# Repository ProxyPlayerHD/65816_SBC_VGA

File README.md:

# 65816 VGA Card
This is a simple VGA Expansion card designed for my 65816 SBC<br>
It uses an `ATF1508AS` CPLD for all the Logic, and 4x `IDT7005S` or `IDT7006S` Dual Port SRAM ICs for a total of either 32kB or 64kB of VRAM. (or something inbetween)

the Logic uploaded here is for 32kB of VRAM, 640x400 Monochrome (1 bit per pixel or "bpp") with an Interrupt every time a frame finished drawing.<br>
Though once i get my hands on some 16kB Chips i'll likely do a few more versions of the Logic and also upload them here.

# Folders
* "Downloaded Libs" contains the symbols and footprints for the KiCad Project
* "Logic" contains the... well Logic for the entire thing. i've included the original .dig file (requires [Digital](https://github.com/hneemann/Digital) to open), and already generated .v (Verilog) and .pof/.jed (program files in case you want to skip setting up Quartus to generate them yourself)
* "Gerbers" contains all required Gerbers to order yourself the PCB

# Misc

regards to the Logic:
the `CA13` line (CPU Address bit 13) is only required when dealing with 8kB DP-SRAM Chips,<br>
and the `VA13` (Video Address bit 13) line is only required when dealing with 16kB DP-SRAM Chips.<br>
also right now the decoding logic puts the VRAM on the CPU side at address `$FF8000`

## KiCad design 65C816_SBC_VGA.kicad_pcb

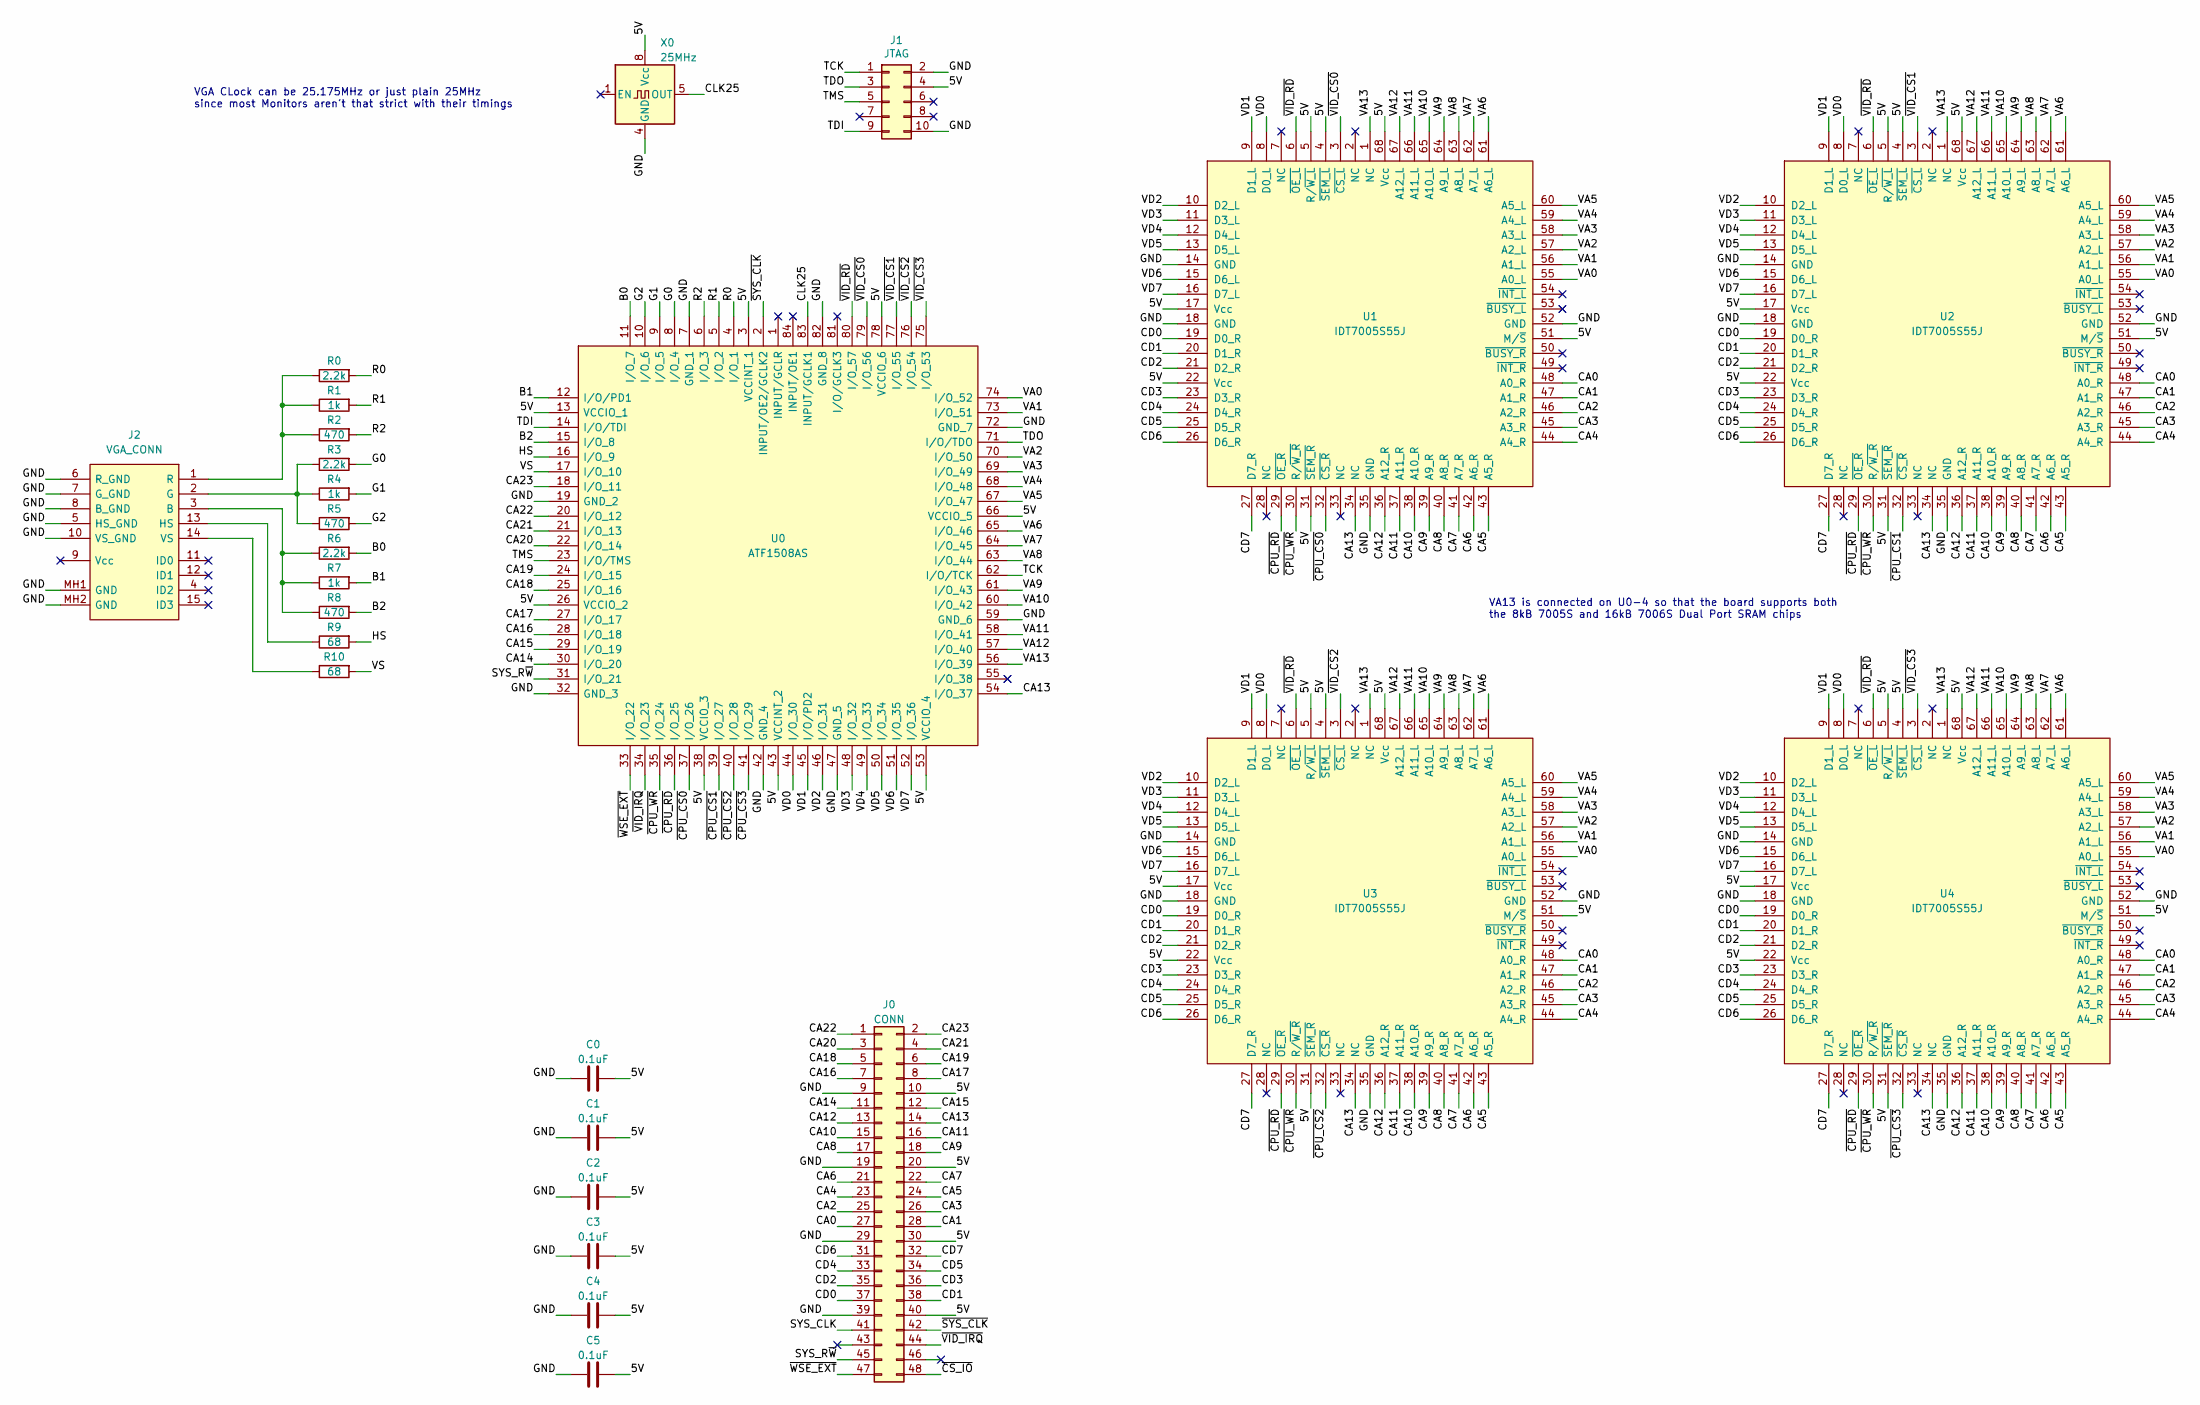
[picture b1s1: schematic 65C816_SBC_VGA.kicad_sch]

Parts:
C0, C1, C2, C3, C4, C5: 0.1uF; C_Disc_D4.3mm_W1.9mm_P5.00mm
J0: CONN; CARD_EDGE
J1: JTAG; PinHeader_2x05_P2.54mm_Vertical
J2: VGA_CONN; Mouser Part Number 156-3315-E
R0, R3, R6: 2.2k; R_Axial_DIN0207_L6.3mm_D2.5mm_P2.54mm_Vertical
R1, R4, R7: 1k; R_Axial_DIN0207_L6.3mm_D2.5mm_P2.54mm_Vertical
R2, R5, R8: 470; R_Axial_DIN0207_L6.3mm_D2.5mm_P2.54mm_Vertical
R9, R10: 68; R_Axial_DIN0207_L6.3mm_D2.5mm_P2.54mm_Vertical
U0: ATF1508AS; PLCC-84_THT-Socket
U1, U2, U3, U4: IDT7005S55J; PLCC-68_THT-Socket
X0: 25MHz; Oscillator_DIP-8

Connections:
/5V: C0.2, C1.2, C2.2, C3.2, C4.2, C5.2, J0.10, J0.20, J0.30, J0.40, J1.4, U0.3 (VCCINT_1), U0.13 (VCCIO_1), U0.26 (VCCIO_2), U0.38 (VCCIO_3), U0.43 (VCCINT_2), U0.53 (VCCIO_4), U0.66 (VCCIO_5), U0.78 (VCCIO_6), U1.4 (~SEM_L), U1.5 (R/~W_L), U1.17 (Vcc), U1.22 (Vcc), U1.31 (~SEM_R), U1.51 (M/~S), U1.68 (Vcc), U2.4 (~SEM_L), U2.5 (R/~W_L), U2.17 (Vcc), U2.22 (Vcc), U2.31 (~SEM_R), U2.51 (M/~S), U2.68 (Vcc), U3.4 (~SEM_L), U3.5 (R/~W_L), U3.17 (Vcc), U3.22 (Vcc), U3.31 (~SEM_R), U3.51 (M/~S), U3.68 (Vcc), U4.4 (~SEM_L), U4.5 (R/~W_L), U4.17 (Vcc), U4.22 (Vcc), U4.31 (~SEM_R), U4.51 (M/~S), U4.68 (Vcc), X0.8 (Vcc)
/B0: R6.2, U0.11 (I/O_7)
/B1: R7.2, U0.12 (I/O/PD1)
/B2: R8.2, U0.15 (I/O_8)
/CA0: J0.27, U1.48 (A0_R), U2.48 (A0_R), U3.48 (A0_R), U4.48 (A0_R)
/CA1: J0.28, U1.47 (A1_R), U2.47 (A1_R), U3.47 (A1_R), U4.47 (A1_R)
/CA2: J0.25, U1.46 (A2_R), U2.46 (A2_R), U3.46 (A2_R), U4.46 (A2_R)
/CA3: J0.26, U1.45 (A3_R), U2.45 (A3_R), U3.45 (A3_R), U4.45 (A3_R)
/CA4: J0.23, U1.44 (A4_R), U2.44 (A4_R), U3.44 (A4_R), U4.44 (A4_R)
/CA5: J0.24, U1.43 (A5_R), U2.43 (A5_R), U3.43 (A5_R), U4.43 (A5_R)
/CA6: J0.21, U1.42 (A6_R), U2.42 (A6_R), U3.42 (A6_R), U4.42 (A6_R)
/CA7: J0.22, U1.41 (A7_R), U2.41 (A7_R), U3.41 (A7_R), U4.41 (A7_R)
/CA8: J0.17, U1.40 (A8_R), U2.40 (A8_R), U3.40 (A8_R), U4.40 (A8_R)
/CA9: J0.18, U1.39 (A9_R), U2.39 (A9_R), U3.39 (A9_R), U4.39 (A9_R)
/CA10: J0.15, U1.38 (A10_R), U2.38 (A10_R), U3.38 (A10_R), U4.38 (A10_R)
/CA11: J0.16, U1.37 (A11_R), U2.37 (A11_R), U3.37 (A11_R), U4.37 (A11_R)
/CA12: J0.13, U1.36 (A12_R), U2.36 (A12_R), U3.36 (A12_R), U4.36 (A12_R)
/CA13: J0.14, U0.54 (I/O_37), U1.34 (NC), U2.34 (NC), U3.34 (NC), U4.34 (NC)
/CA14: J0.11, U0.30 (I/O_20)
/CA15: J0.12, U0.29 (I/O_19)
/CA16: J0.7, U0.28 (I/O_18)
/CA17: J0.8, U0.27 (I/O_17)
/CA18: J0.5, U0.25 (I/O_16)
/CA19: J0.6, U0.24 (I/O_15)
/CA20: J0.3, U0.22 (I/O_14)
/CA21: J0.4, U0.21 (I/O_13)
/CA22: J0.1, U0.20 (I/O_12)
/CA23: J0.2, U0.18 (I/O_11)
/CD0: J0.37, U1.19 (D0_R), U2.19 (D0_R), U3.19 (D0_R), U4.19 (D0_R)
/CD1: J0.38, U1.20 (D1_R), U2.20 (D1_R), U3.20 (D1_R), U4.20 (D1_R)
/CD2: J0.35, U1.21 (D2_R), U2.21 (D2_R), U3.21 (D2_R), U4.21 (D2_R)
/CD3: J0.36, U1.23 (D3_R), U2.23 (D3_R), U3.23 (D3_R), U4.23 (D3_R)
/CD4: J0.33, U1.24 (D4_R), U2.24 (D4_R), U3.24 (D4_R), U4.24 (D4_R)
/CD5: J0.34, U1.25 (D5_R), U2.25 (D5_R), U3.25 (D5_R), U4.25 (D5_R)
/CD6: J0.31, U1.26 (D6_R), U2.26 (D6_R), U3.26 (D6_R), U4.26 (D6_R)
/CD7: J0.32, U1.27 (D7_R), U2.27 (D7_R), U3.27 (D7_R), U4.27 (D7_R)
/CLK25: U0.83 (INPUT/GCLK1), X0.5 (OUT)
/G0: R3.2, U0.8 (I/O_4)
/G1: R4.2, U0.9 (I/O_5)
/G2: R5.2, U0.10 (I/O_6)
/GND: C0.1, C1.1, C2.1, C3.1, C4.1, C5.1, J0.9, J0.19, J0.29, J0.39, J1.2, J1.10, J2.5 (HS_GND), J2.6 (R_GND), J2.7 (G_GND), J2.8 (B_GND), J2.10 (VS_GND), J2.MH1 (GND), J2.MH2 (GND), U0.7 (GND_1), U0.19 (GND_2), U0.32 (GND_3), U0.42 (GND_4), U0.47 (GND_5), U0.59 (GND_6), U0.72 (GND_7), U0.82 (GND_8), U1.14 (GND), U1.18 (GND), U1.35 (GND), U1.52 (GND), U2.14 (GND), U2.18 (GND), U2.35 (GND), U2.52 (GND), U3.14 (GND), U3.18 (GND), U3.35 (GND), U3.52 (GND), U4.14 (GND), U4.18 (GND), U4.35 (GND), U4.52 (GND), X0.4 (GND)
/HS: R9.2, U0.16 (I/O_9)
/R0: R0.2, U0.4 (I/O_1)
/R1: R1.2, U0.5 (I/O_2)
/R2: R2.2, U0.6 (I/O_3)
/SYS_CLK: J0.41
/SYS_R~W: J0.45, U0.31 (I/O_21)
/TCK: J1.1, U0.62 (I/O/TCK)
/TDI: J1.9, U0.14 (I/O/TDI)
/TDO: J1.3, U0.71 (I/O/TDO)
/TMS: J1.5, U0.23 (I/O/TMS)
/VA0: U0.74 (I/O_52), U1.55 (A0_L), U2.55 (A0_L), U3.55 (A0_L), U4.55 (A0_L)
/VA1: U0.73 (I/O_51), U1.56 (A1_L), U2.56 (A1_L), U3.56 (A1_L), U4.56 (A1_L)
/VA2: U0.70 (I/O_50), U1.57 (A2_L), U2.57 (A2_L), U3.57 (A2_L), U4.57 (A2_L)
/VA3: U0.69 (I/O_49), U1.58 (A3_L), U2.58 (A3_L), U3.58 (A3_L), U4.58 (A3_L)
/VA4: U0.68 (I/O_48), U1.59 (A4_L), U2.59 (A4_L), U3.59 (A4_L), U4.59 (A4_L)
/VA5: U0.67 (I/O_47), U1.60 (A5_L), U2.60 (A5_L), U3.60 (A5_L), U4.60 (A5_L)
/VA6: U0.65 (I/O_46), U1.61 (A6_L), U2.61 (A6_L), U3.61 (A6_L), U4.61 (A6_L)
/VA7: U0.64 (I/O_45), U1.62 (A7_L), U2.62 (A7_L), U3.62 (A7_L), U4.62 (A7_L)
/VA8: U0.63 (I/O_44), U1.63 (A8_L), U2.63 (A8_L), U3.63 (A8_L), U4.63 (A8_L)
/VA9: U0.61 (I/O_43), U1.64 (A9_L), U2.64 (A9_L), U3.64 (A9_L), U4.64 (A9_L)
/VA10: U0.60 (I/O_42), U1.65 (A10_L), U2.65 (A10_L), U3.65 (A10_L), U4.65 (A10_L)
/VA11: U0.58 (I/O_41), U1.66 (A11_L), U2.66 (A11_L), U3.66 (A11_L), U4.66 (A11_L)
/VA12: U0.57 (I/O_40), U1.67 (A12_L), U2.67 (A12_L), U3.67 (A12_L), U4.67 (A12_L)
/VA13: U0.56 (I/O_39), U1.1 (NC), U2.1 (NC), U3.1 (NC), U4.1 (NC)
/VD0: U0.44 (I/O_30), U1.8 (D0_L), U2.8 (D0_L), U3.8 (D0_L), U4.8 (D0_L)
/VD1: U0.45 (I/O/PD2), U1.9 (D1_L), U2.9 (D1_L), U3.9 (D1_L), U4.9 (D1_L)
/VD2: U0.46 (I/O_31), U1.10 (D2_L), U2.10 (D2_L), U3.10 (D2_L), U4.10 (D2_L)
/VD3: U0.48 (I/O_32), U1.11 (D3_L), U2.11 (D3_L), U3.11 (D3_L), U4.11 (D3_L)
/VD4: U0.49 (I/O_33), U1.12 (D4_L), U2.12 (D4_L), U3.12 (D4_L), U4.12 (D4_L)
/VD5: U0.50 (I/O_34), U1.13 (D5_L), U2.13 (D5_L), U3.13 (D5_L), U4.13 (D5_L)
/VD6: U0.51 (I/O_35), U1.15 (D6_L), U2.15 (D6_L), U3.15 (D6_L), U4.15 (D6_L)
/VD7: U0.52 (I/O_36), U1.16 (D7_L), U2.16 (D7_L), U3.16 (D7_L), U4.16 (D7_L)
/VS: R10.2, U0.17 (I/O_10)
/~CPU_CS0: U0.37 (I/O_26), U1.32 (~CS_R)
/~CPU_CS1: U0.39 (I/O_27), U2.32 (~CS_R)
/~CPU_CS2: U0.40 (I/O_28), U3.32 (~CS_R)
/~CPU_CS3: U0.41 (I/O_29), U4.32 (~CS_R)
/~CPU_RD: U0.36 (I/O_25), U1.29 (~OE_R), U2.29 (~OE_R), U3.29 (~OE_R), U4.29 (~OE_R)
/~CPU_WR: U0.35 (I/O_24), U1.30 (R/~W_R), U2.30 (R/~W_R), U3.30 (R/~W_R), U4.30 (R/~W_R)
/~CS_IO: J0.48
/~SYS_CLK: J0.42, U0.2 (INPUT/OE2/GCLK2)
/~VID_CS0: U0.79 (I/O_56), U1.3 (~CS_L)
/~VID_CS1: U0.77 (I/O_55), U2.3 (~CS_L)
/~VID_CS2: U0.76 (I/O_54), U3.3 (~CS_L)
/~VID_CS3: U0.75 (I/O_53), U4.3 (~CS_L)
/~VID_IRQ: J0.44, U0.34 (I/O_23)
/~VID_RD: U0.80 (I/O_57), U1.6 (~OE_L), U2.6 (~OE_L), U3.6 (~OE_L), U4.6 (~OE_L)
/~WSE_EXT: J0.47, U0.33 (I/O_22)
unnamed: J2.1 (R), R0.1, R1.1, R2.1
unnamed: J2.2 (G), R3.1, R4.1, R5.1
unnamed: J2.3 (B), R6.1, R7.1, R8.1
unnamed: J2.13 (HS), R9.1
unnamed: J2.14 (VS), R10.1

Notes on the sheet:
VGA CLock can be 25.175MHz or just plain 25MHz since most Monitors aren't that strict with their timings
VA13 is connected on U0-4 so that the board supports both the 8kB 7005S and 16kB 7006S Dual Port SRAM chips

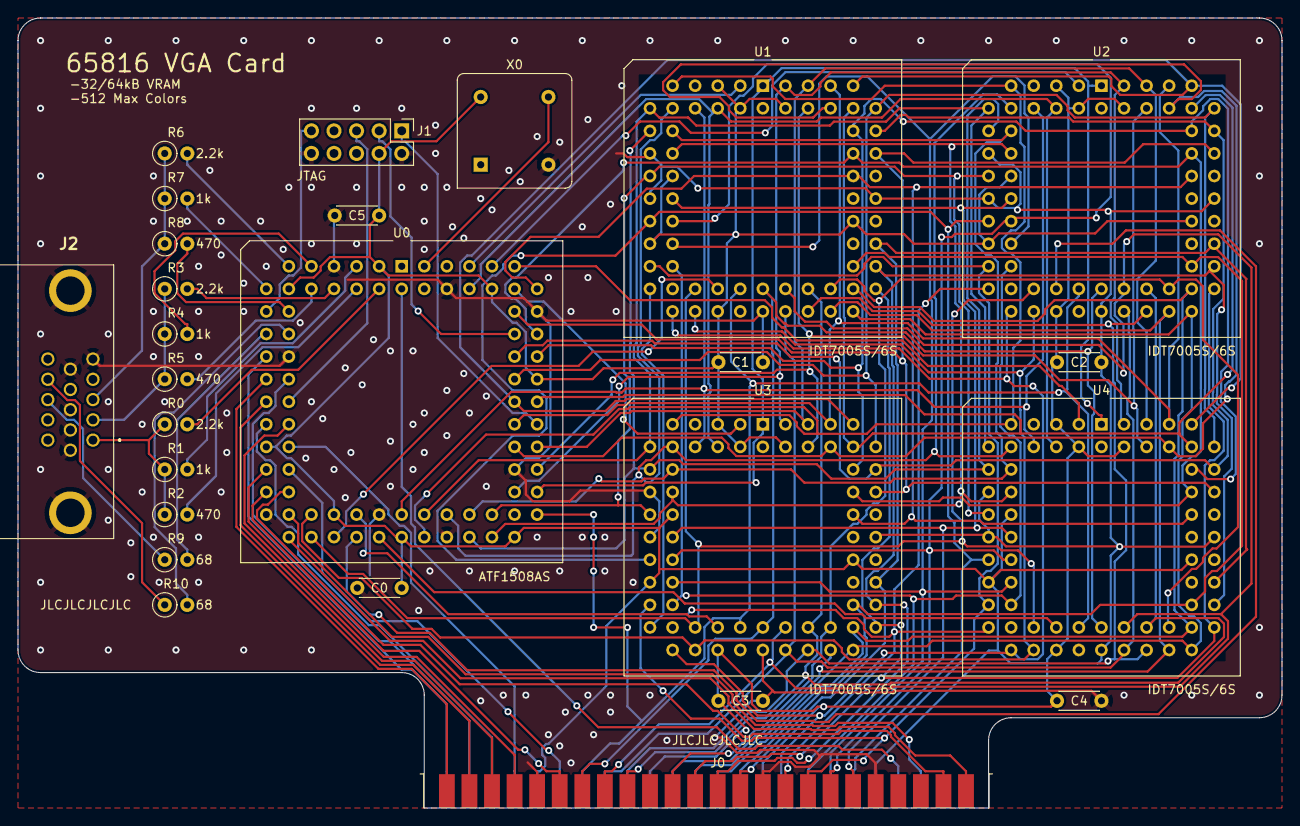
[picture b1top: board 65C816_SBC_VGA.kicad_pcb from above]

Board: 2 copper layers, 142.2 x 88.9 mm, 26 parts (0 on the bottom side), 92 nets.
